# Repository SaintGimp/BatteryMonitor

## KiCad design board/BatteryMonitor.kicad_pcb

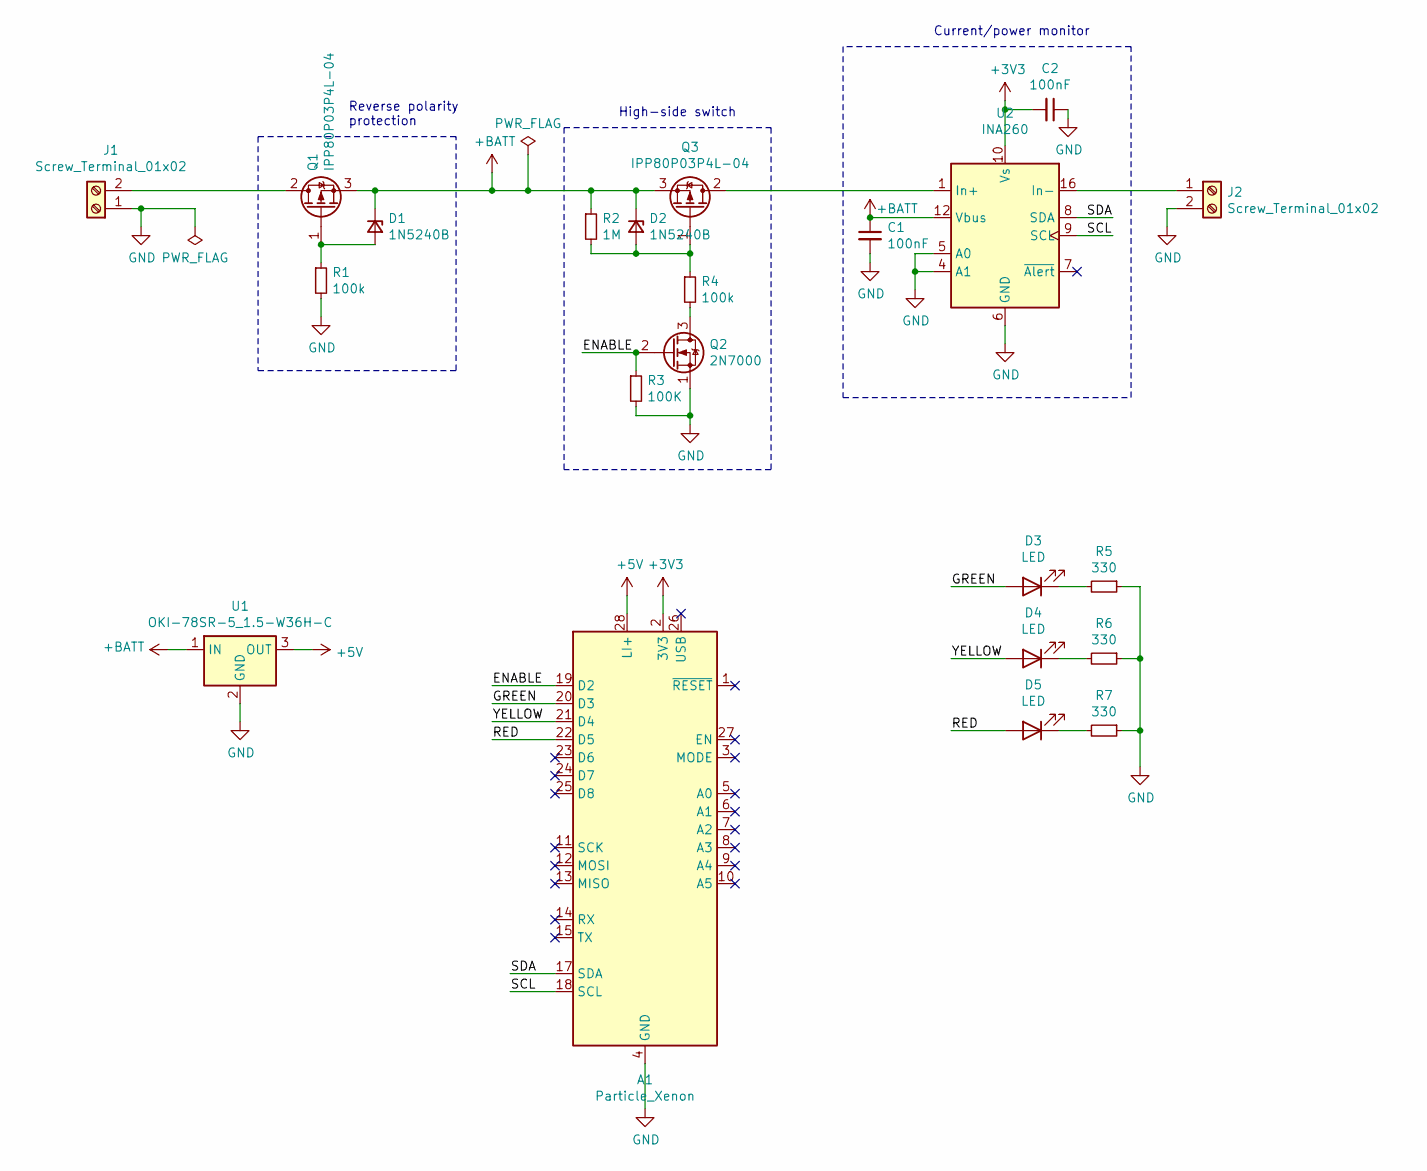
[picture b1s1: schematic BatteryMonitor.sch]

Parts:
A1: Particle_Xenon; Adafruit_Feather
C1, C2: 100nF; C_0805_2012Metric_Pad1.15x1.40mm_HandSolder
D1, D2: 1N5240B; D_DO-35_SOD27_P7.62mm_Horizontal
D3, D4, D5: LED; LED_D3.0mm
J1, J2: Screw_Terminal_01x02; TerminalBlock_Phoenix_MKDS-1,5-2-5.08_1x02_P5.08mm_Horizont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
Q1, Q3: IPP80P03P4L-04; TO-220-3_Horizontal_TabDown
Q2: 2N7000; TO-92_Inline
R1, R4: 100k; R_0805_2012Metric_Pad1.15x1.40mm_HandSolder
R2: 1M; R_0805_2012Metric_Pad1.15x1.40mm_HandSolder
R3: 100K; R_0805_2012Metric_Pad1.15x1.40mm_HandSolder
R5, R6, R7: 330; R_0805_2012Metric_Pad1.15x1.40mm_HandSolder
U1: OKI-78SR-5_1.5-W36H-C; Converter_DCDC_muRata_OKI-78SR_Horizontal
U2: INA260; TSSOP-16_4.4x5mm_P0.65mm

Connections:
+3V3: A1.2 (3V3), C2.2, U2.10 (Vs)
+5V: A1.28 (LI+), U1.3 (OUT)
+BATT: C1.1, D1.1 (K), D2.1 (K), Q1.3 (S), Q3.3 (S), R2.1, U1.1 (IN), U2.12 (Vbus)
/ENABLE: A1.19 (D2), Q2.2 (G), R3.1
/GREEN: A1.20 (D3), D3.2 (A)
/RED: A1.22 (D5), D5.2 (A)
/SCL: A1.18 (SCL), U2.9 (SCL)
/SDA: A1.17 (SDA), U2.8 (SDA)
/YELLOW: A1.21 (D4), D4.2 (A)
GND: A1.4 (GND), C1.2, C2.1, J1.1, J2.2, Q2.1 (S), R1.2, R3.2, R5.1, R6.1, R7.1, U1.2 (GND), U2.4 (A1), U2.5 (A0), U2.6 (GND), U2.11 (GND)
unnamed: D1.2 (A), Q1.1 (G), R1.1
unnamed: D2.2 (A), Q3.1 (G), R2.2, R4.1
unnamed: D3.1 (K), R5.2
unnamed: D4.1 (K), R6.2
unnamed: D5.1 (K), R7.2
unnamed: J1.2, Q1.2 (D)
unnamed: J2.1, U2.14 (In-), U2.15 (In-), U2.16 (In-)
unnamed: Q2.3 (D), R4.2
unnamed: Q3.2 (D), U2.1 (In+), U2.2 (In+), U2.3 (In+)

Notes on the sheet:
Reverse polarity protection
High-side switch
Current/power monitor

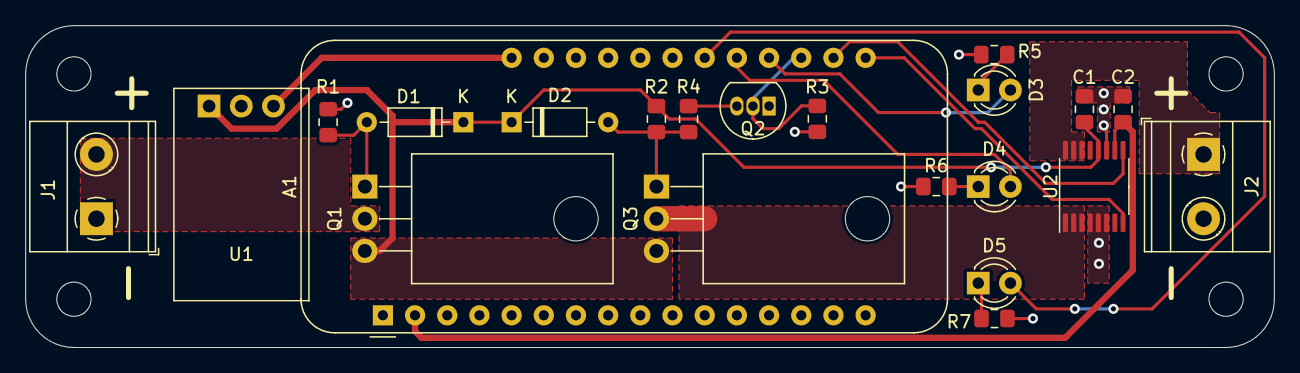
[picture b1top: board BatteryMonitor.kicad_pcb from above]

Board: 2 copper layers, 98.6 x 25.4 mm, 22 parts (0 on the bottom side), 19 nets.

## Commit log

2017-03-04 Module that monitors SLA battery charge level and cuts the supply if the charge gets too low
2020-10-08 V2 schematic
2020-10-08 Assign footprints and begin board layout
2020-10-25 Finish layout, first spin
2020-11-10 New code
2020-11-15 Updated code
2021-06-22 Average the voltage for more consistent response
